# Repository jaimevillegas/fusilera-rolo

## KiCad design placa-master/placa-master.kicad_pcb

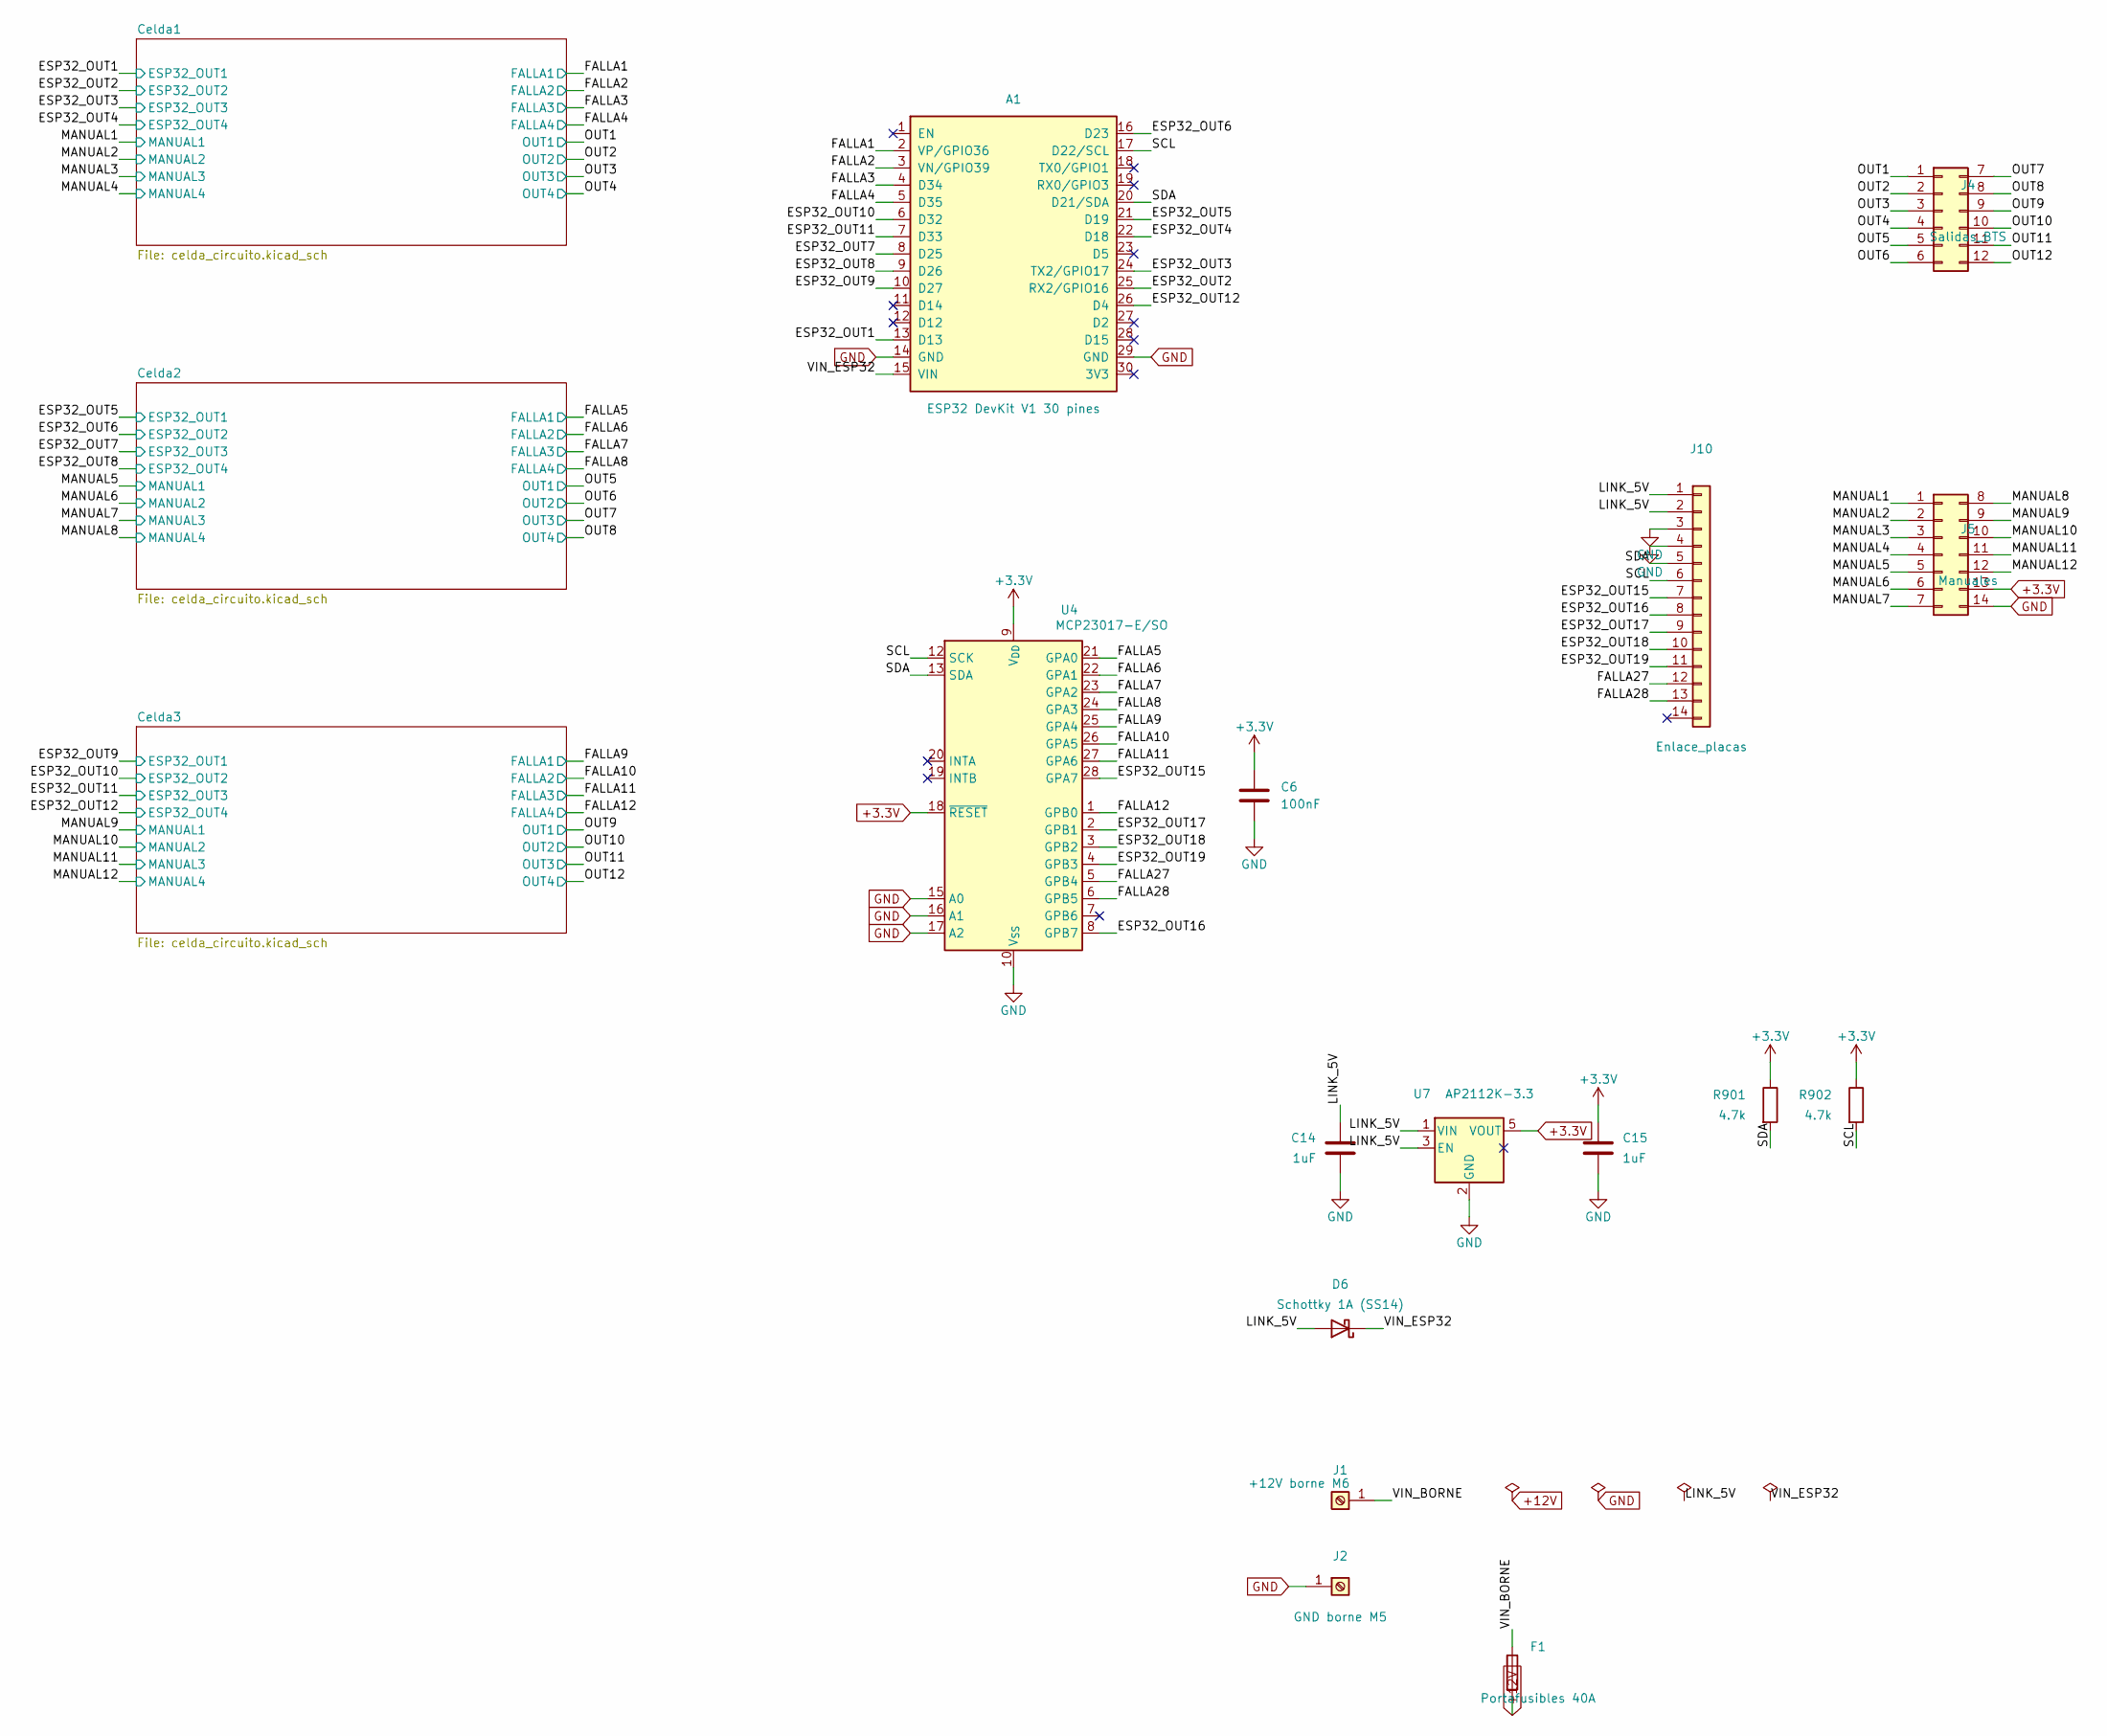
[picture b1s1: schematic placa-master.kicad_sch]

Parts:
A1: ESP32 DevKit V1 30 pines; ESP32_DevKit_30pin_Socket
C6: 100nF; C_0805_2012Metric
C14, C15: 1uF; C_0805_2012Metric
D6: Schottky 1A (SS14); D_SMA
F1: Portafusibles 40A; FuseHolder_2xFaston187_P4.70mm
J1: +12V borne M6; MountingHole_6.4mm_M6_Pad
J2: GND borne M5; MountingHole_5.3mm_M5_Pad
J4: Salidas_BTS; Molex_Mini-Fit_Jr_5569-12A2_2x06_P4.20mm_Horizontal
J5: Manuales; Molex_Micro-Fit_3.0_43045-1400_2x07_P3.00mm_Horizontal
J10: Enlace_placas; JST_XH_B14B-XH-A_1x14_P2.50mm_Vertical
R901, R902: 4.7k; R_0805_2012Metric
U4: MCP23017-E/SO; SOIC-28W_7.5x17.9mm_P1.27mm
U7: AP2112K-3.3; SOT-23-5

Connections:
+3.3V: C6.1, C15.1, J5.13, R901.1, R902.1, U4.9 (V_{DD}), U4.18 (~RESET), U7.5 (VOUT); also elsewhere on the board
+12V: F1.2; also elsewhere on the board
/ESP32_OUT1: A1.13 (D13); also elsewhere on the board
/ESP32_OUT2: A1.25 (RX2/GPIO16); also elsewhere on the board
/ESP32_OUT3: A1.24 (TX2/GPIO17); also elsewhere on the board
/ESP32_OUT4: A1.22 (D18); also elsewhere on the board
/ESP32_OUT5: A1.21 (D19); also elsewhere on the board
/ESP32_OUT6: A1.16 (D23); also elsewhere on the board
/ESP32_OUT7: A1.8 (D25); also elsewhere on the board
/ESP32_OUT8: A1.9 (D26); also elsewhere on the board
/ESP32_OUT9: A1.10 (D27); also elsewhere on the board
/ESP32_OUT10: A1.6 (D32); also elsewhere on the board
/ESP32_OUT11: A1.7 (D33); also elsewhere on the board
/ESP32_OUT12: A1.26 (D4); also elsewhere on the board
/ESP32_OUT15: J10.7, U4.28 (GPA7)
/ESP32_OUT16: J10.8, U4.8 (GPB7)
/ESP32_OUT17: J10.9, U4.2 (GPB1)
/ESP32_OUT18: J10.10, U4.3 (GPB2)
/ESP32_OUT19: J10.11, U4.4 (GPB3)
/FALLA1: A1.2 (VP/GPIO36); also elsewhere on the board
/FALLA2: A1.3 (VN/GPIO39); also elsewhere on the board
/FALLA3: A1.4 (D34); also elsewhere on the board
/FALLA4: A1.5 (D35); also elsewhere on the board
/FALLA5: U4.21 (GPA0); also elsewhere on the board
/FALLA6: U4.22 (GPA1); also elsewhere on the board
/FALLA7: U4.23 (GPA2); also elsewhere on the board
/FALLA8: U4.24 (GPA3); also elsewhere on the board
/FALLA9: U4.25 (GPA4); also elsewhere on the board
/FALLA10: U4.26 (GPA5); also elsewhere on the board
/FALLA11: U4.27 (GPA6); also elsewhere on the board
/FALLA12: U4.1 (GPB0); also elsewhere on the board
/FALLA27: J10.12, U4.5 (GPB4)
/FALLA28: J10.13, U4.6 (GPB5)
/LINK_5V: C14.1, D6.2 (A), J10.1, J10.2, U7.1 (VIN), U7.3 (EN)
/MANUAL1: J5.1; also elsewhere on the board
/MANUAL2: J5.2; also elsewhere on the board
/MANUAL3: J5.3; also elsewhere on the board
/MANUAL4: J5.4; also elsewhere on the board
/MANUAL5: J5.5; also elsewhere on the board
/MANUAL6: J5.6; also elsewhere on the board
/MANUAL7: J5.7; also elsewhere on the board
/MANUAL8: J5.8; also elsewhere on the board
/MANUAL9: J5.9; also elsewhere on the board
/MANUAL10: J5.10; also elsewhere on the board
/MANUAL11: J5.11; also elsewhere on the board
/MANUAL12: J5.12; also elsewhere on the board
/OUT1: J4.1; also elsewhere on the board
/OUT2: J4.2; also elsewhere on the board
/OUT3: J4.3; also elsewhere on the board
/OUT4: J4.4; also elsewhere on the board
/OUT5: J4.5; also elsewhere on the board
/OUT6: J4.6; also elsewhere on the board
/OUT7: J4.7; also elsewhere on the board
/OUT8: J4.8; also elsewhere on the board
/OUT9: J4.9; also elsewhere on the board
/OUT10: J4.10; also elsewhere on the board
/OUT11: J4.11; also elsewhere on the board
/OUT12: J4.12; also elsewhere on the board
/SCL: A1.17 (D22/SCL), J10.6, R902.2, U4.12 (SCK)
/SDA: A1.20 (D21/SDA), J10.5, R901.2, U4.13 (SDA)
/VIN_BORNE: F1.1, J1.1
/VIN_ESP32: A1.15 (VIN), D6.1 (K)
GND: A1.14 (GND), A1.29 (GND), C6.2, C14.2, C15.2, J2.1, J5.14, J10.3, J10.4, U4.10 (V_{SS}), U4.15 (A0), U4.16 (A1), U4.17 (A2), U7.2 (GND); also elsewhere on the board

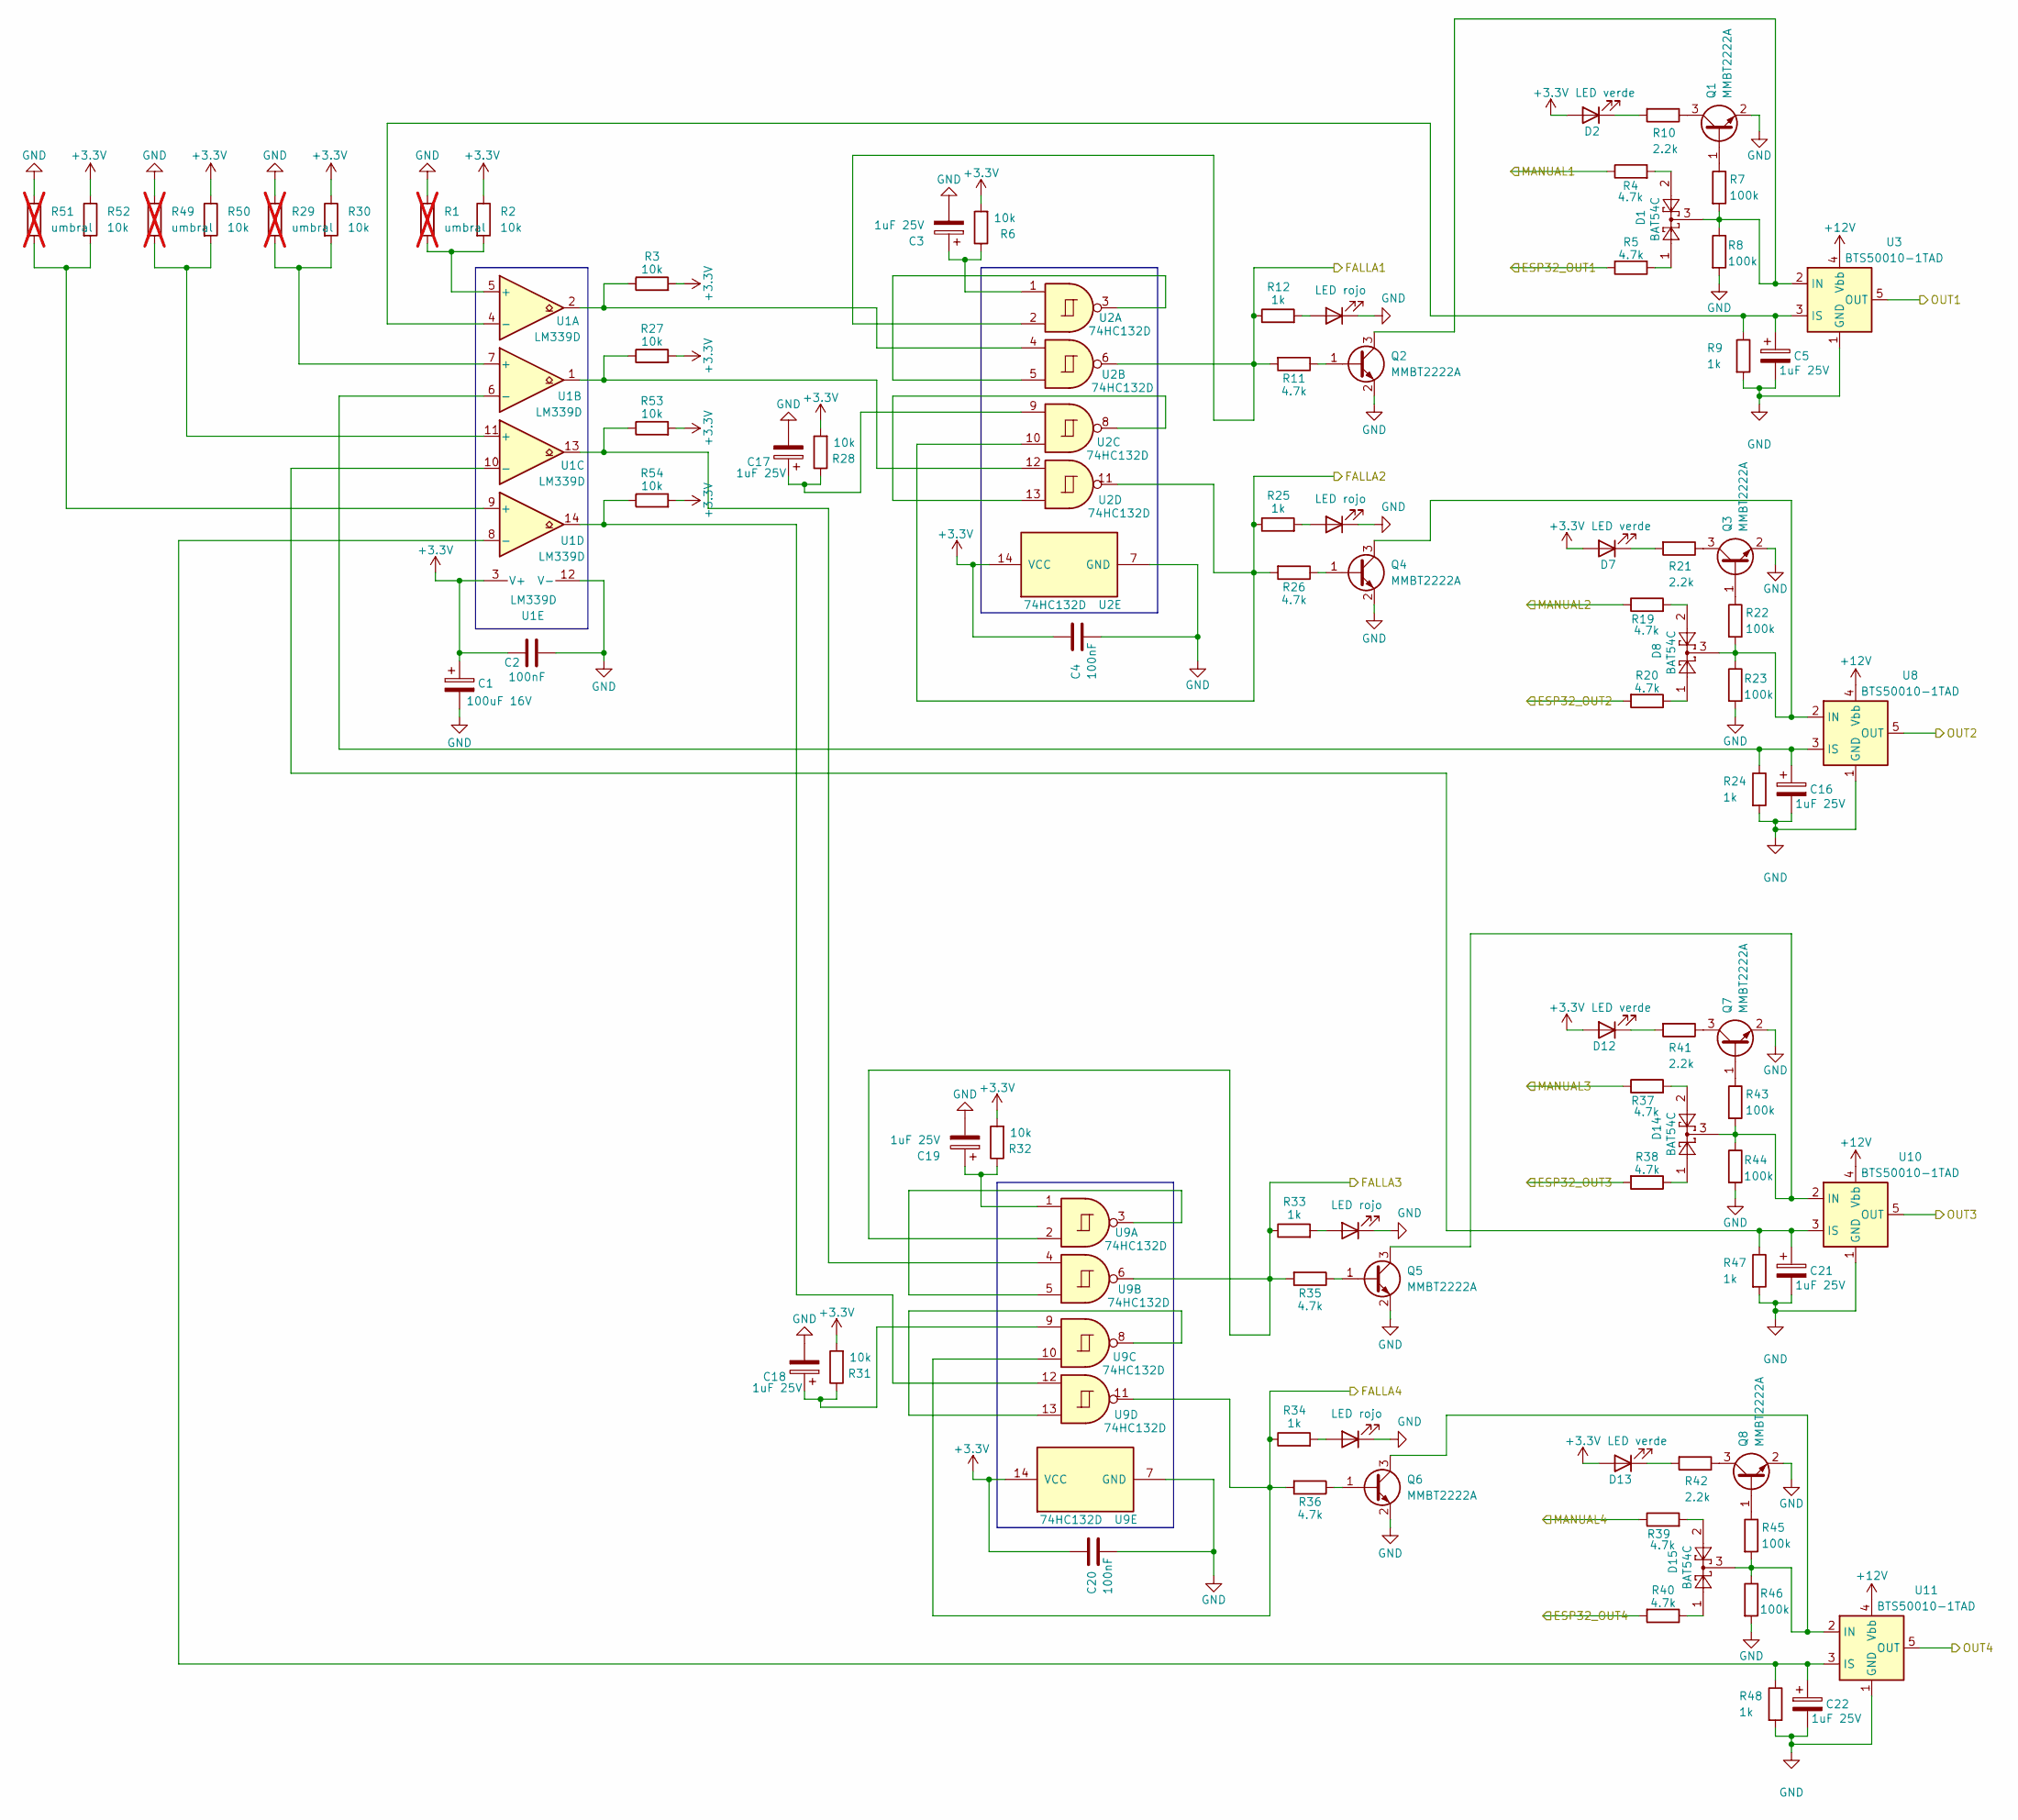
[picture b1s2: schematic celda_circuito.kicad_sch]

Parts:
C1: 100uF 16V; CP_Elec_6.3x5.4
C2, C4, C20: 100nF; C_0805_2012Metric
C3, C5, C16, C17, C18, C19, C21, C22: 1uF 25V; CP_Elec_4x5.4
D1, D8, D14, D15: BAT54C; SOT-23
D2, D7, D12, D13: LED verde; LED_0805_2012Metric
D3, D9, D10, D11: LED rojo; LED_0805_2012Metric
Q1, Q2, Q3, Q4, Q5, Q6, Q7, Q8: MMBT2222A; SOT-23
R1, R29, R49, R51: umbral; R_Axial_DIN0207_L6.3mm_D2.5mm_P10.16mm_Horizontal; not fitted
R2, R3, R6, R27, R28, R30, R31, R32, R50, R52, R53, R54: 10k; R_0805_2012Metric
R4, R5, R11, R19, R20, R26, R35, R36, R37, R38, R39, R40: 4.7k; R_0805_2012Metric
R7, R8, R22, R23, R43, R44, R45, R46: 100k; R_0805_2012Metric
R9, R12, R24, R25, R33, R34, R47, R48: 1k; R_0805_2012Metric
R10, R21, R41, R42: 2.2k; R_0805_2012Metric
U1: LM339D; SOIC-14_3.9x8.7mm_P1.27mm
U2, U9: 74HC132D; SOIC-14_3.9x8.7mm_P1.27mm
U3, U8, U10, U11: BTS50010-1TAD; TO-263-7_TabPin4

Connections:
+3.3V: C1.1, C2.1, C4.1, C20.1, D2.2 (A), D7.2 (A), D12.2 (A), D13.2 (A), R2.1, R3.2, R6.2, R27.2, R28.2, R30.1, R31.2, R32.2, R50.1, R52.1, R53.2, R54.2, U1.3 (V+), U2.14 (VCC), U9.14 (VCC); also elsewhere on the board
+12V: U3.4 (Vbb), U8.4 (Vbb), U10.4 (Vbb), U11.4 (Vbb); also elsewhere on the board
/ESP32_OUT1: R5.2; also elsewhere on the board
/ESP32_OUT2: R20.2; also elsewhere on the board
/ESP32_OUT3: R38.2; also elsewhere on the board
/ESP32_OUT4: R40.2; also elsewhere on the board
/FALLA1: R11.2, R12.1, U2.2, U2.6; also elsewhere on the board
/FALLA2: R25.1, R26.2, U2.10, U2.11; also elsewhere on the board
/FALLA3: R33.1, R35.2, U9.2, U9.6; also elsewhere on the board
/FALLA4: R34.1, R36.2, U9.10, U9.11; also elsewhere on the board
/MANUAL1: R4.1; also elsewhere on the board
/MANUAL2: R19.1; also elsewhere on the board
/MANUAL3: R37.1; also elsewhere on the board
/MANUAL4: R39.1; also elsewhere on the board
/OUT1: U3.5 (OUT), U3.6 (OUT), U3.7 (OUT); also elsewhere on the board
/OUT2: U8.5 (OUT), U8.6 (OUT), U8.7 (OUT); also elsewhere on the board
/OUT3: U10.5 (OUT), U10.6 (OUT), U10.7 (OUT); also elsewhere on the board
/OUT4: U11.5 (OUT), U11.6 (OUT), U11.7 (OUT); also elsewhere on the board
GND: C1.2, C2.2, C3.2, C4.2, C5.2, C16.2, C17.2, C18.2, C19.2, C20.2, C21.2, C22.2, D3.1 (K), D9.1 (K), D10.1 (K), D11.1 (K), Q1.2 (E), Q2.2 (E), Q3.2 (E), Q4.2 (E), Q5.2 (E), Q6.2 (E), Q7.2 (E), Q8.2 (E), R1.1, R8.2, R9.2, R23.2, R24.2, R29.1, R44.2, R46.2, R47.2, R48.2, R49.1, R51.1, U1.12 (V-), U2.7 (GND), U3.1 (GND), U8.1 (GND), U9.7 (GND), U10.1 (GND), U11.1 (GND); also elsewhere on the board
unnamed: C3.1, R6.1, U2.1
unnamed: C17.1, R28.1, U2.9
unnamed: C18.1, R31.1, U9.9
unnamed: C19.1, R32.1, U9.1
unnamed: D1.1, R5.1
unnamed: D1.2, R4.2
unnamed: D2.1 (K), R10.2
unnamed: D3.2 (A), R12.2
unnamed: D7.1 (K), R21.2
unnamed: D8.1, R20.1
unnamed: D8.2, R19.2
unnamed: D9.2 (A), R25.2
unnamed: D10.2 (A), R33.2
unnamed: D11.2 (A), R34.2
unnamed: D12.1 (K), R41.2
unnamed: D13.1 (K), R42.2
unnamed: D14.1, R38.1
unnamed: D14.2, R37.2
unnamed: D15.1, R40.1
unnamed: D15.2, R39.2
unnamed: Q1.1 (B), R7.1
unnamed: Q1.3 (C), R10.1
unnamed: Q2.1 (B), R11.1
unnamed: D1.3, Q2.3 (C), R7.2, R8.1, U3.2 (IN)
unnamed: Q3.1 (B), R22.1
unnamed: Q3.3 (C), R21.1
unnamed: Q4.1 (B), R26.1
unnamed: D8.3, Q4.3 (C), R22.2, R23.1, U8.2 (IN)
unnamed: Q5.1 (B), R35.1
unnamed: D14.3, Q5.3 (C), R43.2, R44.1, U10.2 (IN)
unnamed: Q6.1 (B), R36.1
unnamed: D15.3, Q6.3 (C), R45.2, R46.1, U11.2 (IN)
unnamed: Q7.1 (B), R43.1
unnamed: Q7.3 (C), R41.1
unnamed: Q8.1 (B), R45.1
unnamed: Q8.3 (C), R42.1
unnamed: R3.1, U1.2, U2.4
unnamed: R27.1, U1.1, U2.12
unnamed: R53.1, U1.13, U9.4
unnamed: R54.1, U1.14, U9.12
unnamed: R1.2, R2.2, U1.5 (+)
unnamed: C5.1, R9.1, U1.4 (-), U3.3 (IS)
unnamed: R29.2, R30.2, U1.7 (+)
unnamed: C16.1, R24.1, U1.6 (-), U8.3 (IS)
unnamed: R49.2, R50.2, U1.11 (+)
unnamed: R51.2, R52.2, U1.9 (+)
unnamed: U2.3, U2.5
unnamed: U2.8, U2.13
unnamed: U9.3, U9.5
unnamed: U9.8, U9.13
unnamed: C21.1, R47.1, U1.10 (-), U10.3 (IS)
unnamed: C22.1, R48.1, U1.8 (-), U11.3 (IS)

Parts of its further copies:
C101, C201: 100uF 16V; CP_Elec_6.3x5.4
C102, C104, C120, C202, C204, C220: 100nF; C_0805_2012Metric
C103, C105, C116, C117, C118, C119, C121, C122, C203, C205, C216, C217, C218, C219, C221, C222: 1uF 25V; CP_Elec_4x5.4
D101, D108, D114, D115, D201, D208, D214, D215: BAT54C; SOT-23
D102, D107, D112, D113, D202, D207, D212, D213: LED verde; LED_0805_2012Metric
D103, D109, D110, D111, D203, D209, D210, D211: LED rojo; LED_0805_2012Metric
Q101, Q102, Q103, Q104, Q105, Q106, Q107, Q108, Q201, Q202, Q203, Q204, Q205, Q206, Q207, Q208: MMBT2222A; SOT-23
R101, R129, R149, R151, R201, R229, R249, R251: umbral; R_Axial_DIN0207_L6.3mm_D2.5mm_P10.16mm_Horizontal; not fitted
R102, R103, R106, R127, R128, R130, R131, R132, R150, R152, R153, R154, R202, R203, R206, R227, R228, R230, R231, R232, R250, R252, R253, R254: 10k; R_0805_2012Metric
R104, R105, R111, R119, R120, R126, R135, R136, R137, R138, R139, R140, R204, R205, R211, R219, R220, R226, R235, R236, R237, R238, R239, R240: 4.7k; R_0805_2012Metric
R107, R108, R122, R123, R143, R144, R145, R146, R207, R208, R222, R223, R243, R244, R245, R246: 100k; R_0805_2012Metric
R109, R112, R124, R125, R133, R134, R147, R148, R209, R212, R224, R225, R233, R234, R247, R248: 1k; R_0805_2012Metric
R110, R121, R141, R142, R210, R221, R241, R242: 2.2k; R_0805_2012Metric
U101, U201: LM339D; SOIC-14_3.9x8.7mm_P1.27mm
U102, U109, U202, U209: 74HC132D; SOIC-14_3.9x8.7mm_P1.27mm
U103, U108, U110, U111, U203, U208, U210, U211: BTS50010-1TAD; TO-263-7_TabPin4

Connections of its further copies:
+3.3V: C101.1, C102.1, C104.1, C120.1, C201.1, C202.1, C204.1, C220.1, D102.2 (A), D107.2 (A), D112.2 (A), D113.2 (A), D202.2 (A), D207.2 (A), D212.2 (A), D213.2 (A), R102.1, R103.2, R106.2, R127.2, R128.2, R130.1, R131.2, R132.2, R150.1, R152.1, R153.2, R154.2, R202.1, R203.2, R206.2, R227.2, R228.2, R230.1, R231.2, R232.2, R250.1, R252.1, R253.2, R254.2, U101.3 (V+), U102.14 (VCC), U109.14 (VCC), U201.3 (V+), U202.14 (VCC), U209.14 (VCC); also elsewhere on the board
+12V: U103.4 (Vbb), U108.4 (Vbb), U110.4 (Vbb), U111.4 (Vbb), U203.4 (Vbb), U208.4 (Vbb), U210.4 (Vbb), U211.4 (Vbb); also elsewhere on the board
/ESP32_OUT5: R105.2; also elsewhere on the board
/ESP32_OUT6: R120.2; also elsewhere on the board
/ESP32_OUT7: R138.2; also elsewhere on the board
/ESP32_OUT8: R140.2; also elsewhere on the board
/ESP32_OUT9: R205.2; also elsewhere on the board
/ESP32_OUT10: R220.2; also elsewhere on the board
/ESP32_OUT11: R238.2; also elsewhere on the board
/ESP32_OUT12: R240.2; also elsewhere on the board
/FALLA5: R111.2, R112.1, U102.2, U102.6; also elsewhere on the board
/FALLA6: R125.1, R126.2, U102.10, U102.11; also elsewhere on the board
/FALLA7: R133.1, R135.2, U109.2, U109.6; also elsewhere on the board
/FALLA8: R134.1, R136.2, U109.10, U109.11; also elsewhere on the board
/FALLA9: R211.2, R212.1, U202.2, U202.6; also elsewhere on the board
/FALLA10: R225.1, R226.2, U202.10, U202.11; also elsewhere on the board
/FALLA11: R233.1, R235.2, U209.2, U209.6; also elsewhere on the board
/FALLA12: R234.1, R236.2, U209.10, U209.11; also elsewhere on the board
/MANUAL5: R104.1; also elsewhere on the board
/MANUAL6: R119.1; also elsewhere on the board
/MANUAL7: R137.1; also elsewhere on the board
/MANUAL8: R139.1; also elsewhere on the board
/MANUAL9: R204.1; also elsewhere on the board
/MANUAL10: R219.1; also elsewhere on the board
/MANUAL11: R237.1; also elsewhere on the board
/MANUAL12: R239.1; also elsewhere on the board
/OUT5: U103.5 (OUT), U103.6 (OUT), U103.7 (OUT); also elsewhere on the board
/OUT6: U108.5 (OUT), U108.6 (OUT), U108.7 (OUT); also elsewhere on the board
/OUT7: U110.5 (OUT), U110.6 (OUT), U110.7 (OUT); also elsewhere on the board
/OUT8: U111.5 (OUT), U111.6 (OUT), U111.7 (OUT); also elsewhere on the board
/OUT9: U203.5 (OUT), U203.6 (OUT), U203.7 (OUT); also elsewhere on the board
/OUT10: U208.5 (OUT), U208.6 (OUT), U208.7 (OUT); also elsewhere on the board
/OUT11: U210.5 (OUT), U210.6 (OUT), U210.7 (OUT); also elsewhere on the board
/OUT12: U211.5 (OUT), U211.6 (OUT), U211.7 (OUT); also elsewhere on the board
GND: C101.2, C102.2, C103.2, C104.2, C105.2, C116.2, C117.2, C118.2, C119.2, C120.2, C121.2, C122.2, C201.2, C202.2, C203.2, C204.2, C205.2, C216.2, C217.2, C218.2, C219.2, C220.2, C221.2, C222.2, D103.1 (K), D109.1 (K), D110.1 (K), D111.1 (K), D203.1 (K), D209.1 (K), D210.1 (K), D211.1 (K), Q101.2 (E), Q102.2 (E), Q103.2 (E), Q104.2 (E), Q105.2 (E), Q106.2 (E), Q107.2 (E), Q108.2 (E), Q201.2 (E), Q202.2 (E), Q203.2 (E), Q204.2 (E), Q205.2 (E), Q206.2 (E), Q207.2 (E), Q208.2 (E), R101.1, R108.2, R109.2, R123.2, R124.2, R129.1, R144.2, R146.2, R147.2, R148.2, R149.1, R151.1, R201.1, R208.2, R209.2, R223.2, R224.2, R229.1, R244.2, R246.2, R247.2, R248.2, R249.1, R251.1, U101.12 (V-), U102.7 (GND), U103.1 (GND), U108.1 (GND), U109.7 (GND), U110.1 (GND), U111.1 (GND), U201.12 (V-), U202.7 (GND), U203.1 (GND), U208.1 (GND), U209.7 (GND), U210.1 (GND), U211.1 (GND); also elsewhere on the board
unnamed: C103.1, R106.1, U102.1
unnamed: C117.1, R128.1, U102.9
unnamed: C118.1, R131.1, U109.9
unnamed: C119.1, R132.1, U109.1
unnamed: C203.1, R206.1, U202.1
unnamed: C217.1, R228.1, U202.9
unnamed: C218.1, R231.1, U209.9
unnamed: C219.1, R232.1, U209.1
unnamed: D101.1, R105.1
unnamed: D101.2, R104.2
unnamed: D102.1 (K), R110.2
unnamed: D103.2 (A), R112.2
unnamed: D107.1 (K), R121.2
unnamed: D108.1, R120.1
unnamed: D108.2, R119.2
unnamed: D109.2 (A), R125.2
unnamed: D110.2 (A), R133.2
unnamed: D111.2 (A), R134.2
unnamed: D112.1 (K), R141.2
unnamed: D113.1 (K), R142.2
unnamed: D114.1, R138.1
unnamed: D114.2, R137.2
unnamed: D115.1, R140.1
unnamed: D115.2, R139.2
unnamed: D201.1, R205.1
unnamed: D201.2, R204.2
unnamed: D202.1 (K), R210.2
unnamed: D203.2 (A), R212.2
unnamed: D207.1 (K), R221.2
unnamed: D208.1, R220.1
unnamed: D208.2, R219.2
unnamed: D209.2 (A), R225.2
unnamed: D210.2 (A), R233.2
unnamed: D211.2 (A), R234.2
unnamed: D212.1 (K), R241.2
unnamed: D213.1 (K), R242.2
unnamed: D214.1, R238.1
unnamed: D214.2, R237.2
unnamed: D215.1, R240.1
unnamed: D215.2, R239.2
unnamed: Q101.1 (B), R107.1
unnamed: Q101.3 (C), R110.1
unnamed: Q102.1 (B), R111.1
unnamed: D101.3, Q102.3 (C), R107.2, R108.1, U103.2 (IN)
unnamed: Q103.1 (B), R122.1
unnamed: Q103.3 (C), R121.1
unnamed: Q104.1 (B), R126.1
unnamed: D108.3, Q104.3 (C), R122.2, R123.1, U108.2 (IN)
unnamed: Q105.1 (B), R135.1
unnamed: D114.3, Q105.3 (C), R143.2, R144.1, U110.2 (IN)
unnamed: Q106.1 (B), R136.1
unnamed: D115.3, Q106.3 (C), R145.2, R146.1, U111.2 (IN)
unnamed: Q107.1 (B), R143.1
unnamed: Q107.3 (C), R141.1
unnamed: Q108.1 (B), R145.1
unnamed: Q108.3 (C), R142.1
unnamed: Q201.1 (B), R207.1
unnamed: Q201.3 (C), R210.1
unnamed: Q202.1 (B), R211.1
unnamed: D201.3, Q202.3 (C), R207.2, R208.1, U203.2 (IN)
unnamed: Q203.1 (B), R222.1
unnamed: Q203.3 (C), R221.1
unnamed: Q204.1 (B), R226.1
unnamed: D208.3, Q204.3 (C), R222.2, R223.1, U208.2 (IN)
unnamed: Q205.1 (B), R235.1
unnamed: D214.3, Q205.3 (C), R243.2, R244.1, U210.2 (IN)
unnamed: Q206.1 (B), R236.1
unnamed: D215.3, Q206.3 (C), R245.2, R246.1, U211.2 (IN)
unnamed: Q207.1 (B), R243.1
unnamed: Q207.3 (C), R241.1
unnamed: Q208.1 (B), R245.1
unnamed: Q208.3 (C), R242.1
unnamed: R103.1, U101.2, U102.4
unnamed: R127.1, U101.1, U102.12
unnamed: R153.1, U101.13, U109.4
unnamed: R154.1, U101.14, U109.12
unnamed: R203.1, U201.2, U202.4
unnamed: R227.1, U201.1, U202.12
unnamed: R253.1, U201.13, U209.4
unnamed: R254.1, U201.14, U209.12
unnamed: R101.2, R102.2, U101.5 (+)
unnamed: C105.1, R109.1, U101.4 (-), U103.3 (IS)
unnamed: R129.2, R130.2, U101.7 (+)
unnamed: C116.1, R124.1, U101.6 (-), U108.3 (IS)
unnamed: R149.2, R150.2, U101.11 (+)
unnamed: C121.1, R147.1, U101.10 (-), U110.3 (IS)
unnamed: R151.2, R152.2, U101.9 (+)
unnamed: C122.1, R148.1, U101.8 (-), U111.3 (IS)
unnamed: U102.3, U102.5
unnamed: U102.8, U102.13
unnamed: U109.3, U109.5
unnamed: U109.8, U109.13
unnamed: R201.2, R202.2, U201.5 (+)
unnamed: C205.1, R209.1, U201.4 (-), U203.3 (IS)
unnamed: R229.2, R230.2, U201.7 (+)
unnamed: C216.1, R224.1, U201.6 (-), U208.3 (IS)
unnamed: R249.2, R250.2, U201.11 (+)
unnamed: C221.1, R247.1, U201.10 (-), U210.3 (IS)
unnamed: R251.2, R252.2, U201.9 (+)
unnamed: C222.1, R248.1, U201.8 (-), U211.3 (IS)
unnamed: U202.3, U202.5
unnamed: U202.8, U202.13
unnamed: U209.3, U209.5
unnamed: U209.8, U209.13

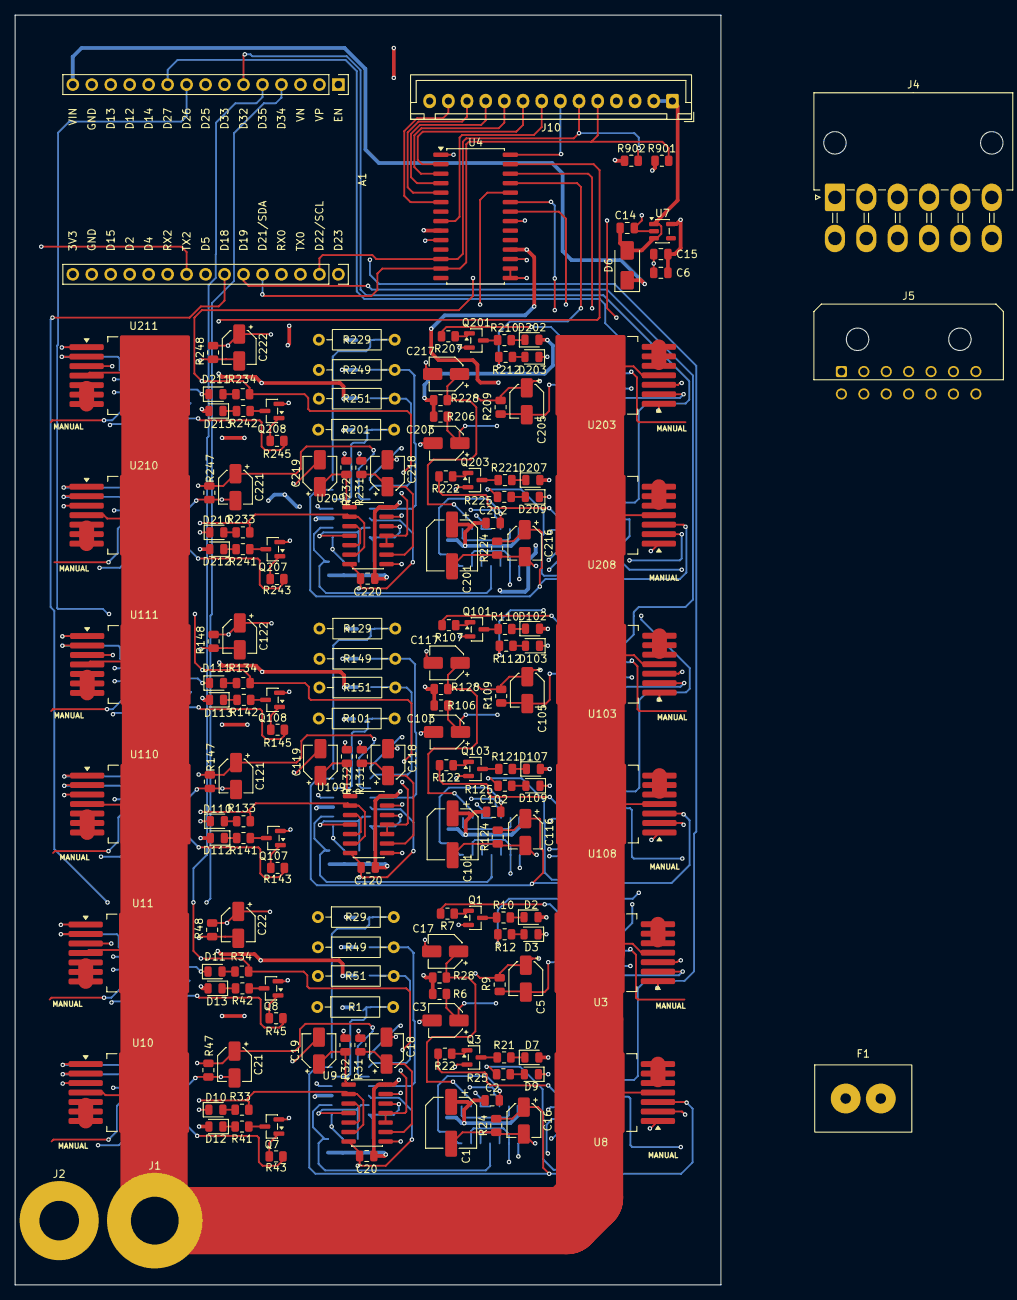
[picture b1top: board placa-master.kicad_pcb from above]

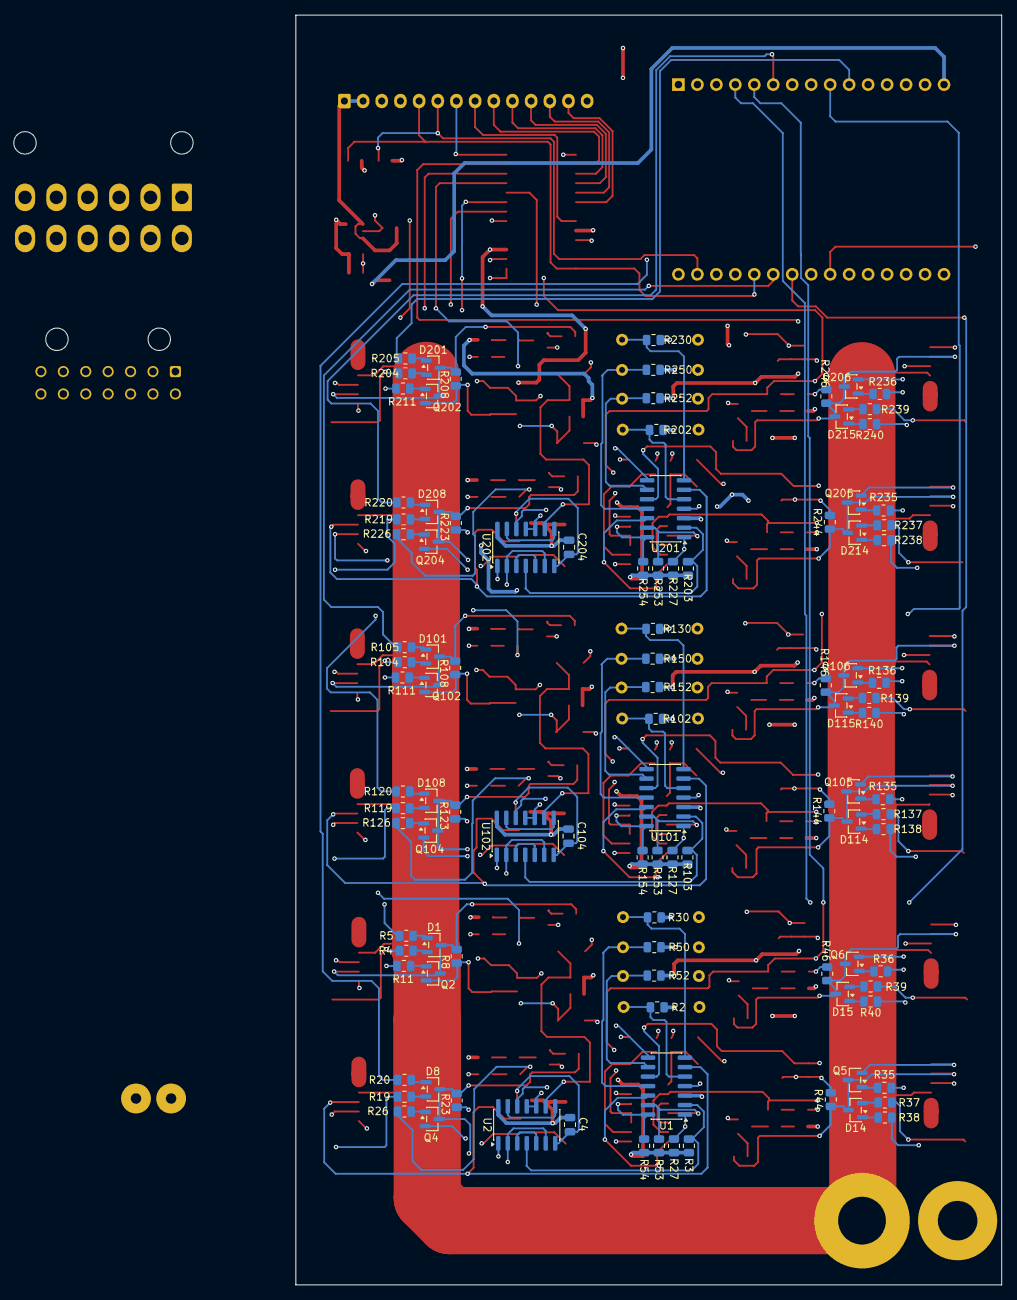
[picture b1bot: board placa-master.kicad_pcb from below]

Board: 4 copper layers, 94.5 x 170.0 mm, 276 parts (105 on the bottom side), 219 nets.
